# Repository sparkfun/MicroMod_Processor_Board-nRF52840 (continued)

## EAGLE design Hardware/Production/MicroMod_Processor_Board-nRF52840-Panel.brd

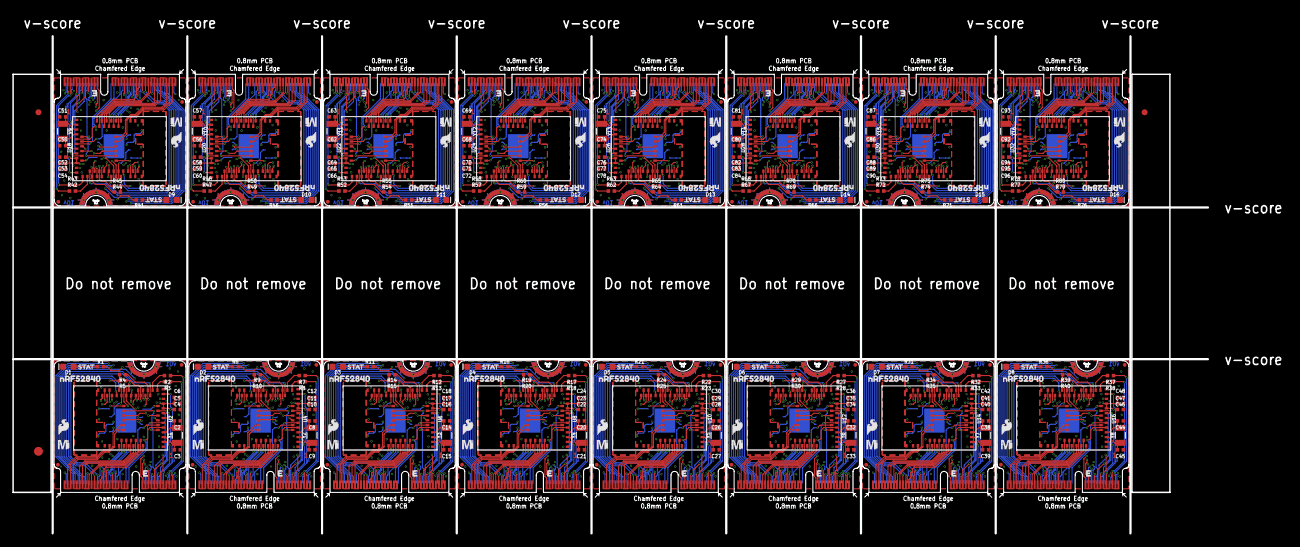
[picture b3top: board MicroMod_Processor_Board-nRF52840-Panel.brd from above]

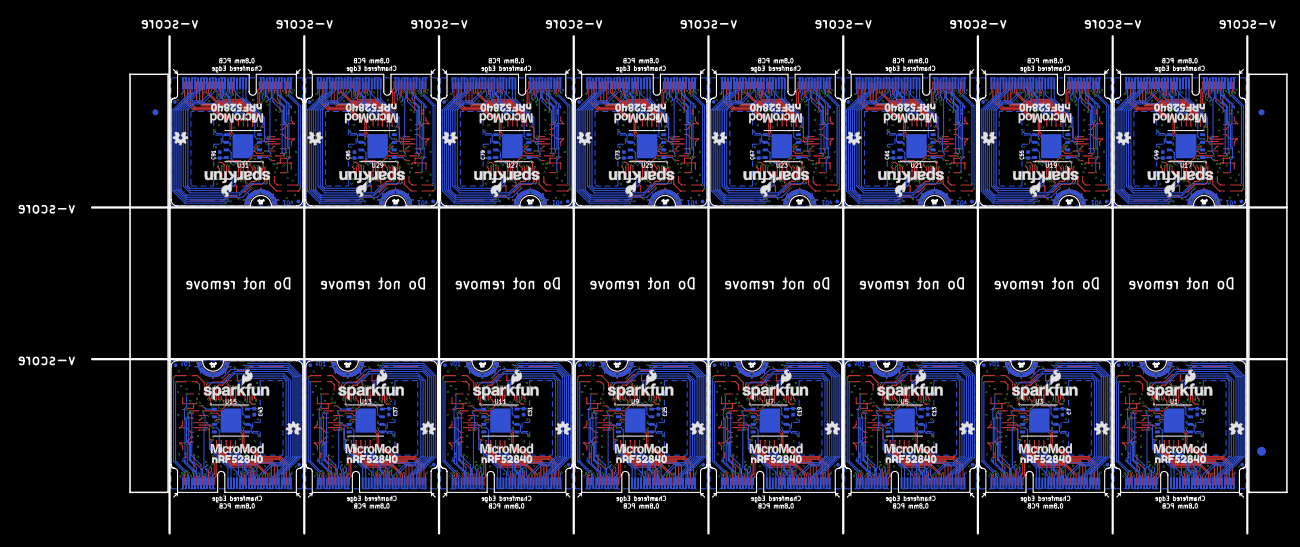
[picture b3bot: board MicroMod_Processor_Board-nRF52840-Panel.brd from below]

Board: 4 copper layers, 199.6 x 83.1 mm, 454 parts (131 on the bottom side), 928 nets.

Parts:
C1, C6, C7, C12, C13, C18, C19, C24, C25, C30, C31, C36, C37, C42, C43, C48, C49, C54, C55, C60, C61, C66, C67, C72, C73, C78, C79, C84, C85, C90, C91, C96: 0.1uF; 0402-TIGHT
C2, C3, C8, C9, C14, C15, C20, C21, C26, C27, C32, C33, C38, C39, C44, C45, C50, C51, C56, C57, C62, C63, C68, C69, C74, C75, C80, C81, C86, C87, C92, C93: 15pF; 0402-TIGHT
C4, C5, C10, C11, C16, C17, C22, C23, C28, C29, C34, C35, C40, C41, C46, C47, C52, C53, C58, C59, C64, C65, C70, C71, C76, C77, C82, C83, C88, C89, C94, C95: 10uF; 0402-TIGHT
D1, D2, D3, D4, D5, D6, D7, D8, D9, D10, D11, D12, D13, D14, D15, D16: BLUE; LED-0603
E$1, E$2, E$3, E$4: FIDUCIAL-1X2
E$5, E$6: FIDUCIAL-1.5X3
FD1, FD2, FD3, FD4, FD5, FD6, FD7, FD8, FD9, FD10, FD11, FD12, FD13, FD14, FD15, FD16, FD17, FD18, FD19, FD20, FD21, FD22, FD23, FD24, FD25, FD26, FD27, FD28, FD29, FD30, FD31, FD32, FD33, FD34, FD35, FD36, FD37, FD38, FD39, FD40, FD41, FD42, FD43, FD44, FD45, FD46, FD47, FD48, FD49, FD50, FD51, FD52, FD53, FD54, FD55, FD56, FD57, FD58, FD59, FD60, FD61, FD62, FD63, FD64: FIDUCIALUFIDUCIAL; FIDUCIAL-MICRO
J1, J2, J3, J4, J5, J6, J7, J8, J9, J10, J11, J12, J13, J14, J15, J16: MICROMOD-2222; M.2-CARD-E-22
LOGO1, LOGO5, LOGO8, LOGO11, LOGO14, LOGO17, LOGO20, LOGO23, LOGO26, LOGO29, LOGO32, LOGO35, LOGO38, LOGO41, LOGO44, LOGO47: SFE_LOGO_NAME_FLAME.1_INCH; SFE_LOGO_NAME_FLAME_.1
LOGO2, LOGO6, LOGO9, LOGO12, LOGO15, LOGO18, LOGO21, LOGO24, LOGO27, LOGO30, LOGO33, LOGO36, LOGO39, LOGO42, LOGO45, LOGO48: SFE_LOGO_FLAME.1_INCH; SFE_LOGO_FLAME_.1
LOGO3, LOGO4, LOGO7, LOGO10, LOGO13, LOGO16, LOGO19, LOGO22, LOGO25, LOGO28, LOGO31, LOGO34, LOGO37, LOGO40, LOGO43, LOGO46: OSHW-LOGOMINI; OSHW-LOGO-MINI
R1, R6, R11, R16, R21, R26, R31, R36, R41, R46, R51, R56, R61, R66, R71, R76: 1k; 0402-TIGHT
R2, R3, R7, R8, R12, R13, R17, R18, R22, R23, R27, R28, R32, R33, R37, R38, R42, R43, R47, R48, R52, R53, R57, R58, R62, R63, R67, R68, R72, R73, R77, R78: 27OHM; 0402-TIGHT
R4, R5, R9, R10, R14, R15, R19, R20, R24, R25, R29, R30, R34, R35, R39, R40, R44, R45, R49, R50, R54, R55, R59, R60, R64, R65, R69, R70, R74, R75, R79, R80: 10k; 0402-TIGHT
U1, U3, U5, U7, U9, U11, U13, U15, U17, U19, U21, U23, U25, U27, U29, U31: W25QXX128MBIT-6X5; WSON-8-6X5
U2, U4, U6, U8, U10, U12, U14, U16, U18, U20, U22, U24, U26, U28, U30, U32: MDBT50Q
U$1, U$7, U$12, U$17, U$22, U$27, U$32, U$37, U$42, U$47, U$52, U$57, U$62, U$67, U$72, U$77: MICROMOD_MI_LOGO_.35
U$2, U$3, U$9, U$10, U$14, U$15, U$19, U$20, U$24, U$25, U$29, U$30, U$34, U$35, U$39, U$40, U$44, U$45, U$49, U$50, U$54, U$55, U$59, U$60, U$64, U$65, U$69, U$70, U$74, U$75, U$79, U$80: NRF528400
U$4, U$6, U$11, U$16, U$21, U$26, U$31, U$36, U$41, U$46, U$51, U$56, U$61, U$66, U$71, U$76: STAT_TO_32
U$5, U$8, U$13, U$18, U$23, U$28, U$33, U$38, U$43, U$48, U$53, U$58, U$63, U$68, U$73, U$78: MICROMOD_LOGO_.35
Y1, Y2, Y3, Y4, Y5, Y6, Y7, Y8, Y9, Y10, Y11, Y12, Y13, Y14, Y15, Y16: 32.768kHz; CRYSTAL-SMD-3.2X1.5MM

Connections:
3.3V: C1.1, C4.1, C5.1, C6.1, J1.2, J1.74, R4.2, R5.2, U1.8, U2.28, U2.30
3.3V1: C7.1, C10.1, C11.1, C12.1, J2.2, J2.74, R9.2, R10.2, U3.8, U4.28, U4.30
3.3V2: C13.1, C16.1, C17.1, C18.1, J3.2, J3.74, R14.2, R15.2, U5.8, U6.28, U6.30
3.3V3: C19.1, C22.1, C23.1, C24.1, J4.2, J4.74, R19.2, R20.2, U7.8, U8.28, U8.30
3.3V4: C25.1, C28.1, C29.1, C30.1, J5.2, J5.74, R24.2, R25.2, U9.8, U10.28, U10.30
3.3V5: C31.1, C34.1, C35.1, C36.1, J6.2, J6.74, R29.2, R30.2, U11.8, U12.28, U12.30
3.3V6: C37.1, C40.1, C41.1, C42.1, J7.2, J7.74, R34.2, R35.2, U13.8, U14.28, U14.30
3.3V7: C43.1, C46.1, C47.1, C48.1, J8.2, J8.74, R39.2, R40.2, U15.8, U16.28, U16.30
3.3V8: C49.1, C52.1, C53.1, C54.1, J9.2, J9.74, R44.2, R45.2, U17.8, U18.28, U18.30
3.3V9: C55.1, C58.1, C59.1, C60.1, J10.2, J10.74, R49.2, R50.2, U19.8, U20.28, U20.30
3.3V10: C61.1, C64.1, C65.1, C66.1, J11.2, J11.74, R54.2, R55.2, U21.8, U22.28, U22.30
3.3V11: C67.1, C70.1, C71.1, C72.1, J12.2, J12.74, R59.2, R60.2, U23.8, U24.28, U24.30
3.3V12: C73.1, C76.1, C77.1, C78.1, J13.2, J13.74, R64.2, R65.2, U25.8, U26.28, U26.30
3.3V13: C79.1, C82.1, C83.1, C84.1, J14.2, J14.74, R69.2, R70.2, U27.8, U28.28, U28.30
3.3V14: C85.1, C88.1, C89.1, C90.1, J15.2, J15.74, R74.2, R75.2, U29.8, U30.28, U30.30
3.3V15: C91.1, C94.1, C95.1, C96.1, J16.2, J16.74, R79.2, R80.2, U31.8, U32.28, U32.30
!BOOT!: J1.11, R4.1, U2.37
!BOOT!1: J2.11, R9.1, U4.37
!BOOT!2: J3.11, R14.1, U6.37
!BOOT!3: J4.11, R19.1, U8.37
!BOOT!4: J5.11, R24.1, U10.37
!BOOT!5: J6.11, R29.1, U12.37
!BOOT!6: J7.11, R34.1, U14.37
!BOOT!7: J8.11, R39.1, U16.37
!BOOT!8: J9.11, R44.1, U18.37
!BOOT!9: J10.11, R49.1, U20.37
!BOOT!10: J11.11, R54.1, U22.37
!BOOT!11: J12.11, R59.1, U24.37
!BOOT!12: J13.11, R64.1, U26.37
!BOOT!13: J14.11, R69.1, U28.37
!BOOT!14: J15.11, R74.1, U30.37
!BOOT!15: J16.11, R79.1, U32.37
!RESET!: J1.6, R5.1, U2.40
!RESET!1: J2.6, R10.1, U4.40
!RESET!2: J3.6, R15.1, U6.40
!RESET!3: J4.6, R20.1, U8.40
!RESET!4: J5.6, R25.1, U10.40
!RESET!5: J6.6, R30.1, U12.40
!RESET!6: J7.6, R35.1, U14.40
!RESET!7: J8.6, R40.1, U16.40
!RESET!8: J9.6, R45.1, U18.40
!RESET!9: J10.6, R50.1, U20.40
!RESET!10: J11.6, R55.1, U22.40
!RESET!11: J12.6, R60.1, U24.40
!RESET!12: J13.6, R65.1, U26.40
!RESET!13: J14.6, R70.1, U28.40
!RESET!14: J15.6, R75.1, U30.40
!RESET!15: J16.6, R80.1, U32.40
ADC0: J1.34, U2.20
ADC1: J1.38, U2.21
ADC2: J2.34, U4.20
ADC3: J2.38, U4.21
ADC4: J3.34, U6.20
ADC5: J3.38, U6.21
ADC6: J4.34, U8.20
ADC7: J4.38, U8.21
ADC8: J5.34, U10.20
ADC9: J5.38, U10.21
ADC10: J6.34, U12.20
ADC11: J6.38, U12.21
ADC12: J7.34, U14.20
ADC13: J7.38, U14.21
ADC14: J8.34, U16.20
ADC15: J8.38, U16.21
ADC16: J9.34, U18.20
ADC17: J9.38, U18.21
ADC18: J10.34, U20.20
ADC19: J10.38, U20.21
ADC20: J11.34, U22.20
ADC21: J11.38, U22.21
ADC22: J12.34, U24.20
ADC23: J12.38, U24.21
ADC24: J13.34, U26.20
ADC25: J13.38, U26.21
ADC26: J14.34, U28.20
ADC27: J14.38, U28.21
ADC28: J15.34, U30.20
ADC29: J15.38, U30.21
ADC30: J16.34, U32.20
ADC31: J16.38, U32.21
ADC_D+: J1.63, U2.10
ADC_D+1: J2.63, U4.10
ADC_D+2: J3.63, U6.10
ADC_D+3: J4.63, U8.10
ADC_D+4: J5.63, U10.10
ADC_D+5: J6.63, U12.10
ADC_D+6: J7.63, U14.10
ADC_D+7: J8.63, U16.10
ADC_D+8: J9.63, U18.10
ADC_D+9: J10.63, U20.10
ADC_D+10: J11.63, U22.10
ADC_D+11: J12.63, U24.10
ADC_D+12: J13.63, U26.10
ADC_D+13: J14.63, U28.10
ADC_D+14: J15.63, U30.10
ADC_D+15: J16.63, U32.10
ADC_D-: J1.65, U2.9
ADC_D-1: J2.65, U4.9
ADC_D-2: J3.65, U6.9
ADC_D-3: J4.65, U8.9
ADC_D-4: J5.65, U10.9
ADC_D-5: J6.65, U12.9
ADC_D-6: J7.65, U14.9
ADC_D-7: J8.65, U16.9
ADC_D-8: J9.65, U18.9
ADC_D-9: J10.65, U20.9
ADC_D-10: J11.65, U22.9
ADC_D-11: J12.65, U24.9
ADC_D-12: J13.65, U26.9
ADC_D-13: J14.65, U28.9
ADC_D-14: J15.65, U30.9
ADC_D-15: J16.65, U32.9
BATT_VIN/1: J2.49, U4.14
BATT_VIN/2: J3.49, U6.14
BATT_VIN/3: J1.49, U2.14
BATT_VIN/4: J4.49, U8.14
BATT_VIN/5: J5.49, U10.14
BATT_VIN/6: J6.49, U12.14
BATT_VIN/7: J7.49, U14.14
BATT_VIN/8: J8.49, U16.14
BATT_VIN/9: J9.49, U18.14
BATT_VIN/10: J10.49, U20.14
BATT_VIN/11: J11.49, U22.14
BATT_VIN/12: J12.49, U24.14
BATT_VIN/13: J13.49, U26.14
BATT_VIN/14: J14.49, U28.14
BATT_VIN/15: J15.49, U30.14
BATT_VIN/16: J16.49, U32.14
CTS1: J1.15, U2.26
CTS2: J2.15, U4.26
CTS3: J3.15, U6.26
CTS4: J4.15, U8.26
CTS5: J5.15, U10.26
CTS6: J6.15, U12.26
CTS7: J7.15, U14.26
CTS8: J8.15, U16.26
CTS9: J9.15, U18.26
CTS10: J10.15, U20.26
CTS11: J11.15, U22.26
CTS12: J12.15, U24.26
CTS13: J13.15, U26.26
CTS14: J14.15, U28.26
CTS15: J15.15, U30.26
CTS16: J16.15, U32.26
D0: J1.10, U2.16
D1: J1.18, U2.25
D2: J2.10, U4.16
D3: J2.18, U4.25
D4: J3.10, U6.16
D5: J3.18, U6.25
D6: J4.10, U8.16
D7: J4.18, U8.25
D8: J5.10, U10.16
D9: J5.18, U10.25
D10: J6.10, U12.16
D11: J6.18, U12.25
D12: J7.10, U14.16
D13: J7.18, U14.25
D14: J8.10, U16.16
D15: J8.18, U16.25
D16: J9.10, U18.16
D17: J9.18, U18.25
D18: J10.10, U20.16
D19: J10.18, U20.25
D20: J11.10, U22.16
D21: J11.18, U22.25
D22: J12.10, U24.16
D23: J12.18, U24.25
D24: J13.10, U26.16
D25: J13.18, U26.25
D26: J14.10, U28.16
D27: J14.18, U28.25
D28: J15.10, U30.16
D29: J15.18, U30.25
D30: J16.10, U32.16
D31: J16.18, U32.25
FLASH_!CS!: U1.1, U2.29
FLASH_!CS!1: U3.1, U4.29
FLASH_!CS!2: U5.1, U6.29
FLASH_!CS!3: U7.1, U8.29
FLASH_!CS!4: U9.1, U10.29
FLASH_!CS!5: U11.1, U12.29
FLASH_!CS!6: U13.1, U14.29
FLASH_!CS!7: U15.1, U16.29
FLASH_!CS!8: U17.1, U18.29
FLASH_!CS!9: U19.1, U20.29
FLASH_!CS!10: U21.1, U22.29
FLASH_!CS!11: U23.1, U24.29
FLASH_!CS!12: U25.1, U26.29
FLASH_!CS!13: U27.1, U28.29
FLASH_!CS!14: U29.1, U30.29
FLASH_!CS!15: U31.1, U32.29
GND: C1.2, C2.1, C3.1, C4.2, C5.2, C6.2, D1.C, J1.1, J1.7, J1.33, J1.36, J1.39, J1.45, J1.75, J1.GND1, J1.GND2, J1.GND3, U1.4, U2.1, U2.2, U2.15, U2.33, U2.55
GND1: C7.2, C8.1, C9.1, C10.2, C11.2, C12.2, D2.C, J2.1, J2.7, J2.33, J2.36, J2.39, J2.45, J2.75, J2.GND1, J2.GND2, J2.GND3, U3.4, U4.1, U4.2, U4.15, U4.33, U4.55
GND2: C13.2, C14.1, C15.1, C16.2, C17.2, C18.2, D3.C, J3.1, J3.7, J3.33, J3.36, J3.39, J3.45, J3.75, J3.GND1, J3.GND2, J3.GND3, U5.4, U6.1, U6.2, U6.15, U6.33, U6.55
GND3: C19.2, C20.1, C21.1, C22.2, C23.2, C24.2, D4.C, J4.1, J4.7, J4.33, J4.36, J4.39, J4.45, J4.75, J4.GND1, J4.GND2, J4.GND3, U7.4, U8.1, U8.2, U8.15, U8.33, U8.55
GND4: C25.2, C26.1, C27.1, C28.2, C29.2, C30.2, D5.C, J5.1, J5.7, J5.33, J5.36, J5.39, J5.45, J5.75, J5.GND1, J5.GND2, J5.GND3, U9.4, U10.1, U10.2, U10.15, U10.33, U10.55
GND5: C31.2, C32.1, C33.1, C34.2, C35.2, C36.2, D6.C, J6.1, J6.7, J6.33, J6.36, J6.39, J6.45, J6.75, J6.GND1, J6.GND2, J6.GND3, U11.4, U12.1, U12.2, U12.15, U12.33, U12.55
GND6: C37.2, C38.1, C39.1, C40.2, C41.2, C42.2, D7.C, J7.1, J7.7, J7.33, J7.36, J7.39, J7.45, J7.75, J7.GND1, J7.GND2, J7.GND3, U13.4, U14.1, U14.2, U14.15, U14.33, U14.55
GND7: C43.2, C44.1, C45.1, C46.2, C47.2, C48.2, D8.C, J8.1, J8.7, J8.33, J8.36, J8.39, J8.45, J8.75, J8.GND1, J8.GND2, J8.GND3, U15.4, U16.1, U16.2, U16.15, U16.33, U16.55
GND8: C49.2, C50.1, C51.1, C52.2, C53.2, C54.2, D9.C, J9.1, J9.7, J9.33, J9.36, J9.39, J9.45, J9.75, J9.GND1, J9.GND2, J9.GND3, U17.4, U18.1, U18.2, U18.15, U18.33, U18.55
GND9: C55.2, C56.1, C57.1, C58.2, C59.2, C60.2, D10.C, J10.1, J10.7, J10.33, J10.36, J10.39, J10.45, J10.75, J10.GND1, J10.GND2, J10.GND3, U19.4, U20.1, U20.2, U20.15, U20.33, U20.55
GND10: C61.2, C62.1, C63.1, C64.2, C65.2, C66.2, D11.C, J11.1, J11.7, J11.33, J11.36, J11.39, J11.45, J11.75, J11.GND1, J11.GND2, J11.GND3, U21.4, U22.1, U22.2, U22.15, U22.33, U22.55
GND11: C67.2, C68.1, C69.1, C70.2, C71.2, C72.2, D12.C, J12.1, J12.7, J12.33, J12.36, J12.39, J12.45, J12.75, J12.GND1, J12.GND2, J12.GND3, U23.4, U24.1, U24.2, U24.15, U24.33, U24.55
GND12: C73.2, C74.1, C75.1, C76.2, C77.2, C78.2, D13.C, J13.1, J13.7, J13.33, J13.36, J13.39, J13.45, J13.75, J13.GND1, J13.GND2, J13.GND3, U25.4, U26.1, U26.2, U26.15, U26.33, U26.55
GND13: C79.2, C80.1, C81.1, C82.2, C83.2, C84.2, D14.C, J14.1, J14.7, J14.33, J14.36, J14.39, J14.45, J14.75, J14.GND1, J14.GND2, J14.GND3, U27.4, U28.1, U28.2, U28.15, U28.33, U28.55
GND14: C85.2, C86.1, C87.1, C88.2, C89.2, C90.2, D15.C, J15.1, J15.7, J15.33, J15.36, J15.39, J15.45, J15.75, J15.GND1, J15.GND2, J15.GND3, U29.4, U30.1, U30.2, U30.15, U30.33, U30.55
GND15: C91.2, C92.1, C93.1, C94.2, C95.2, C96.2, D16.C, J16.1, J16.7, J16.33, J16.36, J16.39, J16.45, J16.75, J16.GND1, J16.GND2, J16.GND3, U31.4, U32.1, U32.2, U32.15, U32.33, U32.55
GPIO0: J1.40, U2.8
GPIO1: J1.42, U2.7
GPIO2: J1.44, U2.6
GPIO3: J1.46, U2.5
GPIO4: J1.48, U2.4
GPIO5: J1.73, U2.3
GPIO6: J1.71, U2.57
GPIO7: J1.69, U2.56
GPIO8: J2.73, U4.3
GPIO9: J2.69, U4.56
GPIO10: J2.71, U4.57
GPIO11: J2.42, U4.7
GPIO12: J2.46, U4.5
GPIO13: J2.44, U4.6
GPIO14: J2.48, U4.4
GPIO15: J2.40, U4.8
GPIO16: J3.73, U6.3
GPIO17: J3.69, U6.56
GPIO18: J3.71, U6.57
GPIO19: J3.42, U6.7
GPIO20: J3.46, U6.5
GPIO21: J3.44, U6.6
GPIO22: J3.48, U6.4
GPIO23: J3.40, U6.8
GPIO24: J4.73, U8.3
GPIO25: J4.69, U8.56
GPIO26: J4.71, U8.57
GPIO27: J4.42, U8.7
GPIO28: J4.46, U8.5
GPIO29: J4.44, U8.6
GPIO30: J4.48, U8.4
GPIO31: J4.40, U8.8
GPIO32: J5.73, U10.3
GPIO33: J5.69, U10.56
GPIO34: J5.71, U10.57
GPIO35: J5.42, U10.7
GPIO36: J5.46, U10.5
GPIO37: J5.44, U10.6
GPIO38: J5.48, U10.4
GPIO39: J5.40, U10.8
GPIO40: J6.73, U12.3
GPIO41: J6.69, U12.56
GPIO42: J6.71, U12.57
GPIO43: J6.42, U12.7
GPIO44: J6.46, U12.5
GPIO45: J6.44, U12.6
GPIO46: J6.48, U12.4
GPIO47: J6.40, U12.8
GPIO48: J7.73, U14.3
GPIO49: J7.69, U14.56
GPIO50: J7.71, U14.57
GPIO51: J7.42, U14.7
GPIO52: J7.46, U14.5
GPIO53: J7.44, U14.6
GPIO54: J7.48, U14.4
GPIO55: J7.40, U14.8
GPIO56: J8.73, U16.3
GPIO57: J8.69, U16.56
GPIO58: J8.71, U16.57
GPIO59: J8.42, U16.7
GPIO60: J8.46, U16.5
GPIO61: J8.44, U16.6
GPIO62: J8.48, U16.4
GPIO63: J8.40, U16.8
GPIO64: J9.73, U18.3
GPIO65: J9.69, U18.56
GPIO66: J9.71, U18.57
GPIO67: J9.42, U18.7
GPIO68: J9.46, U18.5
GPIO69: J9.44, U18.6
GPIO70: J9.48, U18.4
GPIO71: J9.40, U18.8
GPIO72: J10.73, U20.3
GPIO73: J10.69, U20.56
GPIO74: J10.71, U20.57
GPIO75: J10.42, U20.7
GPIO76: J10.46, U20.5
GPIO77: J10.44, U20.6
GPIO78: J10.48, U20.4
GPIO79: J10.40, U20.8
GPIO80: J11.73, U22.3
GPIO81: J11.69, U22.56
GPIO82: J11.71, U22.57
GPIO83: J11.42, U22.7
GPIO84: J11.46, U22.5
GPIO85: J11.44, U22.6
GPIO86: J11.48, U22.4
GPIO87: J11.40, U22.8
GPIO88: J12.73, U24.3
GPIO89: J12.69, U24.56
GPIO90: J12.71, U24.57
GPIO91: J12.42, U24.7
GPIO92: J12.46, U24.5
GPIO93: J12.44, U24.6
GPIO94: J12.48, U24.4
GPIO95: J12.40, U24.8
GPIO96: J13.73, U26.3
GPIO97: J13.69, U26.56
GPIO98: J13.71, U26.57
GPIO99: J13.42, U26.7
GPIO100: J13.46, U26.5
GPIO101: J13.44, U26.6
GPIO102: J13.48, U26.4
GPIO103: J13.40, U26.8
GPIO104: J14.73, U28.3
GPIO105: J14.69, U28.56
GPIO106: J14.71, U28.57
GPIO107: J14.42, U28.7
GPIO108: J14.46, U28.5
GPIO109: J14.44, U28.6
GPIO110: J14.48, U28.4
GPIO111: J14.40, U28.8
GPIO112: J15.73, U30.3
GPIO113: J15.69, U30.56
GPIO114: J15.71, U30.57
GPIO115: J15.42, U30.7
GPIO116: J15.46, U30.5
GPIO117: J15.44, U30.6
GPIO118: J15.48, U30.4
GPIO119: J15.40, U30.8
GPIO120: J16.73, U32.3
GPIO121: J16.69, U32.56
GPIO122: J16.71, U32.57
GPIO123: J16.42, U32.7
GPIO124: J16.46, U32.5
GPIO125: J16.44, U32.6
GPIO126: J16.48, U32.4
GPIO127: J16.40, U32.8
I2C_!INT!: J1.16, U2.60
I2C_!INT!1: J2.16, U4.60
I2C_!INT!2: J3.16, U6.60
I2C_!INT!3: J4.16, U8.60
I2C_!INT!4: J5.16, U10.60
I2C_!INT!5: J6.16, U12.60
I2C_!INT!6: J7.16, U14.60
I2C_!INT!7: J8.16, U16.60
I2C_!INT!8: J9.16, U18.60
I2C_!INT!9: J10.16, U20.60
I2C_!INT!10: J11.16, U22.60
I2C_!INT!11: J12.16, U24.60
I2C_!INT!12: J13.16, U26.60
I2C_!INT!13: J14.16, U28.60
I2C_!INT!14: J15.16, U30.60
I2C_!INT!15: J16.16, U32.60
LED_BUILTIN: R1.2, U2.23
LED_BUILTIN1: R6.2, U4.23
LED_BUILTIN2: R11.2, U6.23
LED_BUILTIN3: R16.2, U8.23
LED_BUILTIN4: R21.2, U10.23
LED_BUILTIN5: R26.2, U12.23
LED_BUILTIN6: R31.2, U14.23
LED_BUILTIN7: R36.2, U16.23
LED_BUILTIN8: R41.2, U18.23
LED_BUILTIN9: R46.2, U20.23
LED_BUILTIN10: R51.2, U22.23
LED_BUILTIN11: R56.2, U24.23
LED_BUILTIN12: R61.2, U26.23
LED_BUILTIN13: R66.2, U28.23
LED_BUILTIN14: R71.2, U30.23
LED_BUILTIN15: R76.2, U32.23
unnamed: R2.2, U2.35
unnamed: D1.A, R1.1
unnamed: R3.2, U2.34
unnamed: C3.2, U2.17, Y1.P$1
unnamed: D2.A, R6.1
unnamed: C2.2, U2.18, Y1.P$2
unnamed: R7.2, U4.35
unnamed: R8.2, U4.34
unnamed: C9.2, U4.17, Y2.P$1
unnamed: C8.2, U4.18, Y2.P$2
unnamed: D3.A, R11.1
unnamed: R12.2, U6.35
unnamed: R13.2, U6.34
unnamed: C15.2, U6.17, Y3.P$1
unnamed: C14.2, U6.18, Y3.P$2
unnamed: D4.A, R16.1
unnamed: R17.2, U8.35
unnamed: R18.2, U8.34
unnamed: C21.2, U8.17, Y4.P$1
unnamed: C20.2, U8.18, Y4.P$2
unnamed: D5.A, R21.1
unnamed: R22.2, U10.35
unnamed: R23.2, U10.34
unnamed: C27.2, U10.17, Y5.P$1
unnamed: C26.2, U10.18, Y5.P$2
unnamed: D6.A, R26.1
unnamed: R27.2, U12.35
unnamed: R28.2, U12.34
unnamed: C33.2, U12.17, Y6.P$1
unnamed: C32.2, U12.18, Y6.P$2
unnamed: D7.A, R31.1
unnamed: R32.2, U14.35
unnamed: R33.2, U14.34
unnamed: C39.2, U14.17, Y7.P$1
unnamed: C38.2, U14.18, Y7.P$2
unnamed: D8.A, R36.1
unnamed: R37.2, U16.35
unnamed: R38.2, U16.34
unnamed: C45.2, U16.17, Y8.P$1
unnamed: C44.2, U16.18, Y8.P$2
unnamed: D9.A, R41.1
unnamed: R42.2, U18.35
unnamed: R43.2, U18.34
unnamed: C51.2, U18.17, Y9.P$1
unnamed: C50.2, U18.18, Y9.P$2
unnamed: D10.A, R46.1
unnamed: R47.2, U20.35
unnamed: R48.2, U20.34
unnamed: C57.2, U20.17, Y10.P$1
unnamed: C56.2, U20.18, Y10.P$2
unnamed: D11.A, R51.1
unnamed: R52.2, U22.35
unnamed: R53.2, U22.34
unnamed: C63.2, U22.17, Y11.P$1
unnamed: C62.2, U22.18, Y11.P$2
unnamed: D12.A, R56.1
unnamed: R57.2, U24.35
unnamed: R58.2, U24.34
unnamed: C69.2, U24.17, Y12.P$1
unnamed: C68.2, U24.18, Y12.P$2
unnamed: D13.A, R61.1
unnamed: R62.2, U26.35
unnamed: R63.2, U26.34
unnamed: C75.2, U26.17, Y13.P$1
unnamed: C74.2, U26.18, Y13.P$2
unnamed: D14.A, R66.1
unnamed: R67.2, U28.35
unnamed: R68.2, U28.34
unnamed: C81.2, U28.17, Y14.P$1
unnamed: C80.2, U28.18, Y14.P$2
unnamed: D15.A, R71.1
unnamed: R72.2, U30.35
unnamed: R73.2, U30.34
unnamed: C87.2, U30.17, Y15.P$1
unnamed: C86.2, U30.18, Y15.P$2
unnamed: D16.A, R76.1
unnamed: R77.2, U32.35
unnamed: R78.2, U32.34
unnamed: C93.2, U32.17, Y16.P$1
unnamed: C92.2, U32.18, Y16.P$2
NFC1: J1.43, U2.52
NFC2: J1.41, U2.54
NFC3: J2.43, U4.52
NFC4: J2.41, U4.54
NFC5: J3.43, U6.52
NFC6: J3.41, U6.54
NFC7: J4.43, U8.52
NFC8: J4.41, U8.54
NFC9: J5.43, U10.52
NFC10: J5.41, U10.54
NFC11: J6.43, U12.52
NFC12: J6.41, U12.54
NFC13: J7.43, U14.52
NFC14: J7.41, U14.54
NFC15: J8.43, U16.52
NFC16: J8.41, U16.54
NFC17: J9.43, U18.52
NFC18: J9.41, U18.54
NFC19: J10.43, U20.52
NFC20: J10.41, U20.54
NFC21: J11.43, U22.52
NFC22: J11.41, U22.54
NFC23: J12.43, U24.52
NFC24: J12.41, U24.54
NFC25: J13.43, U26.52
NFC26: J13.41, U26.54
NFC27: J14.43, U28.52
NFC28: J14.41, U28.54
NFC29: J15.43, U30.52
NFC30: J15.41, U30.54
NFC31: J16.43, U32.52
NFC32: J16.41, U32.54
PDM_CLK: J1.50, U2.49
PDM_CLK1: J2.50, U4.49
PDM_CLK2: J3.50, U6.49
PDM_CLK3: J4.50, U8.49
PDM_CLK4: J5.50, U10.49
PDM_CLK5: J6.50, U12.49
PDM_CLK6: J7.50, U14.49
PDM_CLK7: J8.50, U16.49
PDM_CLK8: J9.50, U18.49
PDM_CLK9: J10.50, U20.49
PDM_CLK10: J11.50, U22.49
PDM_CLK11: J12.50, U24.49
PDM_CLK12: J13.50, U26.49
PDM_CLK13: J14.50, U28.49
PDM_CLK14: J15.50, U30.49
PDM_CLK15: J16.50, U32.49
PDM_DATA: J1.52, U2.19
PDM_DATA1: J2.52, U4.19
PDM_DATA2: J3.52, U6.19
PDM_DATA3: J4.52, U8.19
PDM_DATA4: J5.52, U10.19
PDM_DATA5: J6.52, U12.19
PDM_DATA6: J7.52, U14.19
PDM_DATA7: J8.52, U16.19
PDM_DATA8: J9.52, U18.19
PDM_DATA9: J10.52, U20.19
PDM_DATA10: J11.52, U22.19
PDM_DATA11: J12.52, U24.19
PDM_DATA12: J13.52, U26.19
PDM_DATA13: J14.52, U28.19
PDM_DATA14: J15.52, U30.19
PDM_DATA15: J16.52, U32.19
PWM0: J1.32, U2.22
PWM1: J1.47, U2.38
PWM2: J2.32, U4.22
PWM3: J2.47, U4.38
PWM4: J3.32, U6.22
PWM5: J3.47, U6.38
PWM6: J4.32, U8.22
PWM7: J4.47, U8.38
PWM8: J5.32, U10.22
PWM9: J5.47, U10.38
PWM10: J6.32, U12.22
PWM11: J6.47, U12.38
PWM12: J7.32, U14.22
PWM13: J7.47, U14.38
PWM14: J8.32, U16.22
PWM15: J8.47, U16.38
PWM16: J9.32, U18.22
PWM17: J9.47, U18.38
PWM18: J10.32, U20.22
PWM19: J10.47, U20.38
PWM20: J11.32, U22.22
PWM21: J11.47, U22.38
PWM22: J12.32, U24.22
PWM23: J12.47, U24.38
PWM24: J13.32, U26.22
PWM25: J13.47, U26.38
PWM26: J14.32, U28.22
PWM27: J14.47, U28.38
PWM28: J15.32, U30.22
PWM29: J15.47, U30.38
PWM30: J16.32, U32.22
PWM31: J16.47, U32.38
RTS1: J1.13, U2.50
RTS2: J2.13, U4.50
RTS3: J3.13, U6.50
RTS4: J4.13, U8.50
RTS5: J5.13, U10.50
RTS6: J6.13, U12.50
RTS7: J7.13, U14.50
RTS8: J8.13, U16.50
RTS9: J9.13, U18.50
RTS10: J10.13, U20.50
RTS11: J11.13, U22.50
RTS12: J12.13, U24.50
RTS13: J13.13, U26.50
RTS14: J14.13, U28.50
RTS15: J15.13, U30.50
RTS16: J16.13, U32.50
RX1: J1.19, U2.41
RX2: J1.20, U2.59
RX3: J2.19, U4.41
RX4: J2.20, U4.59
RX5: J3.19, U6.41
RX6: J3.20, U6.59
RX7: J4.19, U8.41
RX8: J4.20, U8.59
RX9: J5.19, U10.41
RX10: J5.20, U10.59
RX11: J6.19, U12.41
RX12: J6.20, U12.59
RX13: J7.19, U14.41
RX14: J7.20, U14.59
RX15: J8.19, U16.41
RX16: J8.20, U16.59
RX17: J9.19, U18.41
RX18: J9.20, U18.59
RX19: J10.19, U20.41
RX20: J10.20, U20.59
RX21: J11.19, U22.41
RX22: J11.20, U22.59
RX23: J12.19, U24.41
RX24: J12.20, U24.59
RX25: J13.19, U26.41
RX26: J13.20, U26.59
RX27: J14.19, U28.41
RX28: J14.20, U28.59
RX29: J15.19, U30.41
RX30: J15.20, U30.59
RX31: J16.19, U32.41
RX32: J16.20, U32.59
SCL: J1.14, U2.27
SCL1: J1.53, U2.48
SCL2: J2.14, U4.27
SCL3: J2.53, U4.48
SCL4: J3.14, U6.27
SCL5: J3.53, U6.48
SCL6: J4.14, U8.27
SCL7: J4.53, U8.48
SCL8: J5.14, U10.27
SCL9: J5.53, U10.48
SCL10: J6.14, U12.27
SCL11: J6.53, U12.48
SCL12: J7.14, U14.27
SCL13: J7.53, U14.48
SCL14: J8.14, U16.27
SCL15: J8.53, U16.48
SCL16: J9.14, U18.27
SCL17: J9.53, U18.48
SCL18: J10.14, U20.27
SCL19: J10.53, U20.48
SCL20: J11.14, U22.27
SCL21: J11.53, U22.48
SCL22: J12.14, U24.27
SCL23: J12.53, U24.48
SCL24: J13.14, U26.27
SCL25: J13.53, U26.48
SCL26: J14.14, U28.27
SCL27: J14.53, U28.48
SCL28: J15.14, U30.27
SCL29: J15.53, U30.48
SCL30: J16.14, U32.27
SCL31: J16.53, U32.48
SDA: J1.12, U2.24
SDA1: J1.51, U2.61
SDA2: J2.12, U4.24
SDA3: J2.51, U4.61
SDA4: J3.12, U6.24
SDA5: J3.51, U6.61
SDA6: J4.12, U8.24
SDA7: J4.51, U8.61
SDA8: J5.12, U10.24
SDA9: J5.51, U10.61
SDA10: J6.12, U12.24
SDA11: J6.51, U12.61
SDA12: J7.12, U14.24
SDA13: J7.51, U14.61
SDA14: J8.12, U16.24
SDA15: J8.51, U16.61
SDA16: J9.12, U18.24
SDA17: J9.51, U18.61
SDA18: J10.12, U20.24
SDA19: J10.51, U20.61
SDA20: J11.12, U22.24
SDA21: J11.51, U22.61
SDA22: J12.12, U24.24
SDA23: J12.51, U24.61
SDA24: J13.12, U26.24
SDA25: J13.51, U26.61
SDA26: J14.12, U28.24
SDA27: J14.51, U28.61
SDA28: J15.12, U30.24
SDA29: J15.51, U30.61
SDA30: J16.12, U32.24
SDA31: J16.51, U32.61
SDIO_DATA1: J1.66, U1.2, U2.46
SDIO_DATA2: J1.68, U1.3, U2.45
SDIO_DATA3: J2.66, U3.2, U4.46
SDIO_DATA4: J2.68, U3.3, U4.45
SDIO_DATA5: J3.66, U5.2, U6.46
SDIO_DATA6: J3.68, U5.3, U6.45
SDIO_DATA7: J4.66, U7.2, U8.46
SDIO_DATA8: J4.68, U7.3, U8.45
SDIO_DATA9: J5.66, U9.2, U10.46
SDIO_DATA10: J5.68, U9.3, U10.45
SDIO_DATA11: J6.66, U11.2, U12.46
SDIO_DATA12: J6.68, U11.3, U12.45
SDIO_DATA13: J7.66, U13.2, U14.46
SDIO_DATA14: J7.68, U13.3, U14.45
SDIO_DATA15: J8.66, U15.2, U16.46
SDIO_DATA16: J8.68, U15.3, U16.45
SDIO_DATA17: J9.66, U17.2, U18.46
SDIO_DATA18: J9.68, U17.3, U18.45
SDIO_DATA19: J10.66, U19.2, U20.46
SDIO_DATA20: J10.68, U19.3, U20.45
SDIO_DATA21: J11.66, U21.2, U22.46
SDIO_DATA22: J11.68, U21.3, U22.45
SDIO_DATA23: J12.66, U23.2, U24.46
SDIO_DATA24: J12.68, U23.3, U24.45
SDIO_DATA25: J13.66, U25.2, U26.46
SDIO_DATA26: J13.68, U25.3, U26.45
SDIO_DATA27: J14.66, U27.2, U28.46
SDIO_DATA28: J14.68, U27.3, U28.45
SDIO_DATA29: J15.66, U29.2, U30.46
SDIO_DATA30: J15.68, U29.3, U30.45
SDIO_DATA31: J16.66, U31.2, U32.46
SDIO_DATA32: J16.68, U31.3, U32.45
SPI_!CS!: J1.70, U1.7, U2.47
SPI_!CS!1: J1.55, U2.44
SPI_!CS!2: J2.70, U3.7, U4.47
SPI_!CS!3: J2.55, U4.44
SPI_!CS!4: J3.70, U5.7, U6.47
SPI_!CS!5: J3.55, U6.44
SPI_!CS!6: J4.70, U7.7, U8.47
SPI_!CS!7: J4.55, U8.44
SPI_!CS!8: J5.70, U9.7, U10.47
SPI_!CS!9: J5.55, U10.44
SPI_!CS!10: J6.70, U11.7, U12.47
SPI_!CS!11: J6.55, U12.44
SPI_!CS!12: J7.70, U13.7, U14.47
SPI_!CS!13: J7.55, U14.44
SPI_!CS!14: J8.70, U15.7, U16.47
SPI_!CS!15: J8.55, U16.44
SPI_!CS!16: J9.70, U17.7, U18.47
SPI_!CS!17: J9.55, U18.44
SPI_!CS!18: J10.70, U19.7, U20.47
SPI_!CS!19: J10.55, U20.44
SPI_!CS!20: J11.70, U21.7, U22.47
SPI_!CS!21: J11.55, U22.44
SPI_!CS!22: J12.70, U23.7, U24.47
SPI_!CS!23: J12.55, U24.44
SPI_!CS!24: J13.70, U25.7, U26.47
SPI_!CS!25: J13.55, U26.44
SPI_!CS!26: J14.70, U27.7, U28.47
SPI_!CS!27: J14.55, U28.44
SPI_!CS!28: J15.70, U29.7, U30.47
SPI_!CS!29: J15.55, U30.44
SPI_!CS!30: J16.70, U31.7, U32.47
SPI_!CS!31: J16.55, U32.44
SPI_MISO: J1.64, U1.5, U2.43
SPI_MISO1: J1.61, U2.11
SPI_MISO2: J2.64, U3.5, U4.43
SPI_MISO3: J2.61, U4.11
SPI_MISO4: J3.64, U5.5, U6.43
SPI_MISO5: J3.61, U6.11
SPI_MISO6: J4.64, U7.5, U8.43
SPI_MISO7: J4.61, U8.11
SPI_MISO8: J5.64, U9.5, U10.43
SPI_MISO9: J5.61, U10.11
SPI_MISO10: J6.64, U11.5, U12.43
SPI_MISO11: J6.61, U12.11
SPI_MISO12: J7.64, U13.5, U14.43
SPI_MISO13: J7.61, U14.11
SPI_MISO14: J8.64, U15.5, U16.43
SPI_MISO15: J8.61, U16.11
SPI_MISO16: J9.64, U17.5, U18.43
SPI_MISO17: J9.61, U18.11
SPI_MISO18: J10.64, U19.5, U20.43
SPI_MISO19: J10.61, U20.11
SPI_MISO20: J11.64, U21.5, U22.43
SPI_MISO21: J11.61, U22.11
SPI_MISO22: J12.64, U23.5, U24.43
SPI_MISO23: J12.61, U24.11
SPI_MISO24: J13.64, U25.5, U26.43
SPI_MISO25: J13.61, U26.11
SPI_MISO26: J14.64, U27.5, U28.43
SPI_MISO27: J14.61, U28.11
SPI_MISO28: J15.64, U29.5, U30.43
SPI_MISO29: J15.61, U30.11
SPI_MISO30: J16.64, U31.5, U32.43
SPI_MISO31: J16.61, U32.11
SPI_MOSI: J1.62, U2.36
SPI_MOSI1: J1.59, U2.12
SPI_MOSI2: J2.59, U4.12
SPI_MOSI3: J2.62, U4.36
SPI_MOSI4: J3.59, U6.12
SPI_MOSI5: J3.62, U6.36
SPI_MOSI6: J4.59, U8.12
SPI_MOSI7: J4.62, U8.36
SPI_MOSI8: J5.59, U10.12
SPI_MOSI9: J5.62, U10.36
SPI_MOSI10: J6.59, U12.12
SPI_MOSI11: J6.62, U12.36
SPI_MOSI12: J7.59, U14.12
SPI_MOSI13: J7.62, U14.36
SPI_MOSI14: J8.59, U16.12
SPI_MOSI15: J8.62, U16.36
SPI_MOSI16: J9.59, U18.12
SPI_MOSI17: J9.62, U18.36
SPI_MOSI18: J10.59, U20.12
SPI_MOSI19: J10.62, U20.36
SPI_MOSI20: J11.59, U22.12
SPI_MOSI21: J11.62, U22.36
SPI_MOSI22: J12.59, U24.12
SPI_MOSI23: J12.62, U24.36
SPI_MOSI24: J13.59, U26.12
SPI_MOSI25: J13.62, U26.36
SPI_MOSI26: J14.59, U28.12
SPI_MOSI27: J14.62, U28.36
SPI_MOSI28: J15.59, U30.12
SPI_MOSI29: J15.62, U30.36
SPI_MOSI30: J16.59, U32.12
SPI_MOSI31: J16.62, U32.36
SPI_SCK: J1.60, U1.6, U2.42
SPI_SCK1: J1.57, U2.13
SPI_SCK2: J2.57, U4.13
SPI_SCK3: J2.60, U3.6, U4.42
SPI_SCK4: J3.57, U6.13
SPI_SCK5: J3.60, U5.6, U6.42
SPI_SCK6: J4.57, U8.13
SPI_SCK7: J4.60, U7.6, U8.42
SPI_SCK8: J5.57, U10.13
SPI_SCK9: J5.60, U9.6, U10.42
SPI_SCK10: J6.57, U12.13
SPI_SCK11: J6.60, U11.6, U12.42
SPI_SCK12: J7.57, U14.13
SPI_SCK13: J7.60, U13.6, U14.42
SPI_SCK14: J8.57, U16.13
SPI_SCK15: J8.60, U15.6, U16.42
SPI_SCK16: J9.57, U18.13
SPI_SCK17: J9.60, U17.6, U18.42
SPI_SCK18: J10.57, U20.13
SPI_SCK19: J10.60, U19.6, U20.42
SPI_SCK20: J11.57, U22.13
SPI_SCK21: J11.60, U21.6, U22.42
SPI_SCK22: J12.57, U24.13
SPI_SCK23: J12.60, U23.6, U24.42
SPI_SCK24: J13.57, U26.13
SPI_SCK25: J13.60, U25.6, U26.42
SPI_SCK26: J14.57, U28.13
SPI_SCK27: J14.60, U27.6, U28.42
SPI_SCK28: J15.57, U30.13
SPI_SCK29: J15.60, U29.6, U30.42
SPI_SCK30: J16.57, U32.13
SPI_SCK31: J16.60, U31.6, U32.42
SWDCK: J1.21, U2.53
SWDCK1: J2.21, U4.53
SWDCK2: J3.21, U6.53
SWDCK3: J4.21, U8.53
SWDCK4: J5.21, U10.53
SWDCK5: J6.21, U12.53
SWDCK6: J7.21, U14.53
SWDCK7: J8.21, U16.53
SWDCK8: J9.21, U18.53
SWDCK9: J10.21, U20.53
SWDCK10: J11.21, U22.53
SWDCK11: J12.21, U24.53
SWDCK12: J13.21, U26.53
SWDCK13: J14.21, U28.53
SWDCK14: J15.21, U30.53
SWDCK15: J16.21, U32.53
SWDIO: J1.23, U2.51
SWDIO1: J2.23, U4.51
SWDIO2: J3.23, U6.51
SWDIO3: J4.23, U8.51
SWDIO4: J5.23, U10.51
SWDIO5: J6.23, U12.51
SWDIO6: J7.23, U14.51
SWDIO7: J8.23, U16.51
SWDIO8: J9.23, U18.51
SWDIO9: J10.23, U20.51
SWDIO10: J11.23, U22.51
SWDIO11: J12.23, U24.51
SWDIO12: J13.23, U26.51
SWDIO13: J14.23, U28.51
SWDIO14: J15.23, U30.51
SWDIO15: J16.23, U32.51
TX1: J1.17, U2.39
TX2: J1.22, U2.58
TX3: J2.17, U4.39
TX4: J2.22, U4.58
TX5: J3.17, U6.39
TX6: J3.22, U6.58
TX7: J4.17, U8.39
TX8: J4.22, U8.58
TX9: J5.17, U10.39
TX10: J5.22, U10.58
TX11: J6.17, U12.39
TX12: J6.22, U12.58
TX13: J7.17, U14.39
TX14: J7.22, U14.58
TX15: J8.17, U16.39
TX16: J8.22, U16.58
TX17: J9.17, U18.39
TX18: J9.22, U18.58
TX19: J10.17, U20.39
TX20: J10.22, U20.58
TX21: J11.17, U22.39
TX22: J11.22, U22.58
TX23: J12.17, U24.39
TX24: J12.22, U24.58
TX25: J13.17, U26.39
TX26: J13.22, U26.58
TX27: J14.17, U28.39
TX28: J14.22, U28.58
TX29: J15.17, U30.39
TX30: J15.22, U30.58
TX31: J16.17, U32.39
TX32: J16.22, U32.58
USB_D+: J1.3, R2.1
USB_D+1: J2.3, R7.1
USB_D+2: J3.3, R12.1
USB_D+3: J4.3, R17.1
USB_D+4: J5.3, R22.1
USB_D+5: J6.3, R27.1
USB_D+6: J7.3, R32.1
USB_D+7: J8.3, R37.1
USB_D+8: J9.3, R42.1
USB_D+9: J10.3, R47.1
USB_D+10: J11.3, R52.1
USB_D+11: J12.3, R57.1
USB_D+12: J13.3, R62.1
USB_D+13: J14.3, R67.1
USB_D+14: J15.3, R72.1
USB_D+15: J16.3, R77.1
USB_D-: J1.5, R3.1
USB_D-1: J2.5, R8.1
USB_D-2: J3.5, R13.1
USB_D-3: J4.5, R18.1
USB_D-4: J5.5, R23.1
USB_D-5: J6.5, R28.1
USB_D-6: J7.5, R33.1
USB_D-7: J8.5, R38.1
USB_D-8: J9.5, R43.1
USB_D-9: J10.5, R48.1
USB_D-10: J11.5, R53.1
USB_D-11: J12.5, R58.1
USB_D-12: J13.5, R63.1
USB_D-13: J14.5, R68.1
USB_D-14: J15.5, R73.1
USB_D-15: J16.5, R78.1
V_USB: J1.9, U2.32
V_USB1: J2.9, U4.32
V_USB2: J3.9, U6.32
V_USB3: J4.9, U8.32
V_USB4: J5.9, U10.32
V_USB5: J6.9, U12.32
V_USB6: J7.9, U14.32
V_USB7: J8.9, U16.32
V_USB8: J9.9, U18.32
V_USB9: J10.9, U20.32
V_USB10: J11.9, U22.32
V_USB11: J12.9, U24.32
V_USB12: J13.9, U26.32
V_USB13: J14.9, U28.32
V_USB14: J15.9, U30.32
V_USB15: J16.9, U32.32

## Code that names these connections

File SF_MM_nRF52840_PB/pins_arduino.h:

#pragma once
#include <stdint.h>
#include <macros.h>

#ifndef __PINS_ARDUINO__
#define __PINS_ARDUINO__

#define ANALOG_CONFIG

/* Analog reference options
 * Different possibilities available combining Reference and Gain
 */
enum _AnalogReferenceMode
{
  AR_VDD,         // 3.3 V
  AR_INTERNAL,    // 0.6 V
  AR_INTERNAL1V2, // 1.2 V
  AR_INTERNAL2V4  // 2.4 V
};

/* Analog acquisition time options */
enum _AnalogAcquisitionTime
{
  AT_3_US,
  AT_5_US,
  AT_10_US, // Default value
  AT_15_US,
  AT_20_US,
  AT_40_US
};

// Frequency of the board main oscillator
#define VARIANT_MAINOSC (32768ul)

// Master clock frequency
#define VARIANT_MCK (64000000ul)

// Pins
// ----
// Number of pins defined in PinDescription array
#ifdef __cplusplus
extern "C" unsigned int PINCOUNT_fn();
#endif
#define PINS_COUNT (PINCOUNT_fn())
#define NUM_DIGITAL_PINS (48u)
#define NUM_ANALOG_INPUTS (6u)
#define NUM_ANALOG_OUTPUTS (0u)

extern PinName digitalPinToPinName(pin_size_t P);       // add paulvha

// LEDs
// ----
#define PIN_LED (13u)
#define LED_BUILTIN PIN_LED

// Analog pins
// -----------
#define PIN_A0 (4u)
#define PIN_A1 (5u)
#define PIN_A2 (29u)
#define PIN_A3 (28u)
#define PIN_A4 (30u)
#define PIN_A5 (31u)
static const uint8_t A0 = PIN_A0;
static const uint8_t A1 = PIN_A1;
static const uint8_t A2 = PIN_A2;
static const uint8_t A3 = PIN_A3;
static const uint8_t A4 = PIN_A4;
static const uint8_t A5 = PIN_A5;
#define PIN_PWM0 (6u)
#define PIN_PWM1 (16u)
static const uint8_t PWM0 = PIN_PWM0;
static const uint8_t PWM1 = PIN_PWM1;
#define PIN_BATTVIN3 (30u)
static const uint8_t BATTVIN3 = PIN_BATTVIN3;
#define ADC_RESOLUTION 12

// Digital pins
// -----------
#define D0 27
#define D1 40
#define G0 29
#define G1 3
#define G2 45
#define G3 44
#define G4 43
#define G5 17
#define G6 38
#define G7 36
#define G8 46
#define G9 9
#define G10 10

/*
 * Serial interfaces
 */
// Serial (EDBG)
#define PIN_SERIAL_RX1 (42ul)
#define PIN_SERIAL_TX1 (35ul)
//For serial flow control, uncomment lines 189 and 190
#define PIN_SERIAL_RTS1 (34ul)
#define PIN_SERIAL_CTS1 (41ul)

#define PIN_SERIAL_RX2 (37ul)
#define PIN_SERIAL_TX2 (39ul)

// SPI
#define PIN_SPI_CIPO (2u)
#define PIN_SPI_COPI (31u)
#define PIN_SPI_SCK (28u)
#define PIN_SPI_SS (20u)

// //NOTE: this is for onboard flash IC
// #define PIN_SPI_CIPO (21u)
// #define PIN_SPI_COPI (14u)
// #define PIN_SPI_SCK (19u)
// #define PIN_SPI_SS (12u)

static const uint8_t SS = PIN_SPI_SS;
static const uint8_t MOSI = PIN_SPI_COPI;
static const uint8_t MISO = PIN_SPI_CIPO;
static const uint8_t SCK = PIN_SPI_SCK;

#define PIN_SPI_CIPO1 (21u)
#define PIN_SPI_COPI1 (14u)
#define PIN_SPI_SCK1 (19u)
#define PIN_SPI_SS1 (32u)

static const uint8_t SS1 = PIN_SPI_SS1;
static const uint8_t MOSI1 = PIN_SPI_COPI1;
static const uint8_t MISO1 = PIN_SPI_CIPO1;
static const uint8_t SCK1 = PIN_SPI_SCK1;

#define PIN_QSPI_SCK 19
#define PIN_QSPI_CS 14
#define PIN_QSPI_IO0 21
#define PIN_QSPI_IO1 22
#define PIN_QSPI_IO2 23
#define PIN_QSPI_IO3 32

// Wire
#define PIN_WIRE_SDA (8u)
#define PIN_WIRE_SCL (11u)
#define PIN_WIRE_INT (15u)

#define PIN_WIRE_SDA1 (33u)
#define PIN_WIRE_SCL1 (24u)

// PDM Interfaces
// ---------------
#define PIN_PDM_PWR (46)
#define PIN_PDM_CLK (25)
#define PIN_PDM_DIN (26)

// These serial port names are intended to allow libraries and architecture-neutral
// sketches to automatically default to the correct port name for a particular type
// of use.  For example, a GPS module would normally connect to SERIAL_PORT_HARDWARE_OPEN,
// the first hardware serial port whose RX/TX pins are not dedicated to another use.
//
// SERIAL_PORT_MONITOR        Port which normally prints to the Arduino Serial Monitor
//
// SERIAL_PORT_USBVIRTUAL     Port which is USB virtual serial
//
// SERIAL_PORT_LINUXBRIDGE    Port which connects to a Linux system via Bridge library
//
// SERIAL_PORT_HARDWARE       Hardware serial port, physical RX & TX pins.
//
// SERIAL_PORT_HARDWARE_OPEN  Hardware serial ports which are open for use.  Their RX & TX
//                            pins are NOT connected to anything by default.
#define SERIAL_PORT_USBVIRTUAL SerialUSB
#define SERIAL_PORT_MONITOR SerialUSB
#define SERIAL_PORT_HARDWARE Serial1
#define SERIAL_PORT_HARDWARE_OPEN Serial1

// Mbed specific defines
#define SERIAL_HOWMANY 2
#define SERIAL1_TX (digitalPinToPinName(PIN_SERIAL_TX1))
#define SERIAL1_RX (digitalPinToPinName(PIN_SERIAL_RX1))
//Uncomment the following two lines if you want to implement serial flow control
// #define SERIAL1_RTS (digitalPinToPinName(PIN_SERIAL_RTS1))
// #define SERIAL1_CTS (digitalPinToPinName(PIN_SERIAL_CTS1))
#define SERIAL2_TX (digitalPinToPinName(PIN_SERIAL_TX2))
#define SERIAL2_RX (digitalPinToPinName(PIN_SERIAL_RX2))

#define SERIAL_CDC 1
#define HAS_UNIQUE_ISERIAL_DESCRIPTOR
#define BOARD_VENDORID 0x2341
#define BOARD_PRODUCTID 0x805a
#define BOARD_NAME "Nano 33 BLE"

#define DFU_MAGIC_SERIAL_ONLY_RESET 0xb0

#define WIRE_HOWMANY 2

#define I2C_SDA (digitalPinToPinName(PIN_WIRE_SDA))
#define I2C_SCL (digitalPinToPinName(PIN_WIRE_SCL))
#define I2C_SDA1 (digitalPinToPinName(PIN_WIRE_SDA1))
#define I2C_SCL1 (digitalPinToPinName(PIN_WIRE_SCL1))

#define SPI_HOWMANY 2

#define SPI_MISO (digitalPinToPinName(PIN_SPI_CIPO))
#define SPI_MOSI (digitalPinToPinName(PIN_SPI_COPI))
#define SPI_SCK (digitalPinToPinName(PIN_SPI_SCK))

#define SPI_MISO1 (digitalPinToPinName(PIN_SPI_CIPO1))
#define SPI_MOSI1 (digitalPinToPinName(PIN_SPI_COPI1))
#define SPI_SCK1 (digitalPinToPinName(PIN_SPI_SCK1))

#define digitalPinToPort(P) (digitalPinToPinName(P) / 32)

uint8_t getUniqueSerialNumber(uint8_t *name);
void _ontouch1200bps_();

#endif //__PINS_ARDUINO__

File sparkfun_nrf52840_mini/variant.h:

/*
  Copyright (c) 2014-2015 Arduino LLC.  All right reserved.
  Copyright (c) 2016 Sandeep Mistry All right reserved.
  Copyright (c) 2018, Adafruit Industries (adafruit.com)

  This library is free software; you can redistribute it and/or
  modify it under the terms of the GNU Lesser General Public
  License as published by the Free Software Foundation; either
  version 2.1 of the License, or (at your option) any later version.
  This library is distributed in the hope that it will be useful,
  but WITHOUT ANY WARRANTY; without even the implied warranty of
  MERCHANTABILITY or FITNESS FOR A PARTICULAR PURPOSE.
  See the GNU Lesser General Public License for more details.
  You should have received a copy of the GNU Lesser General Public
  License along with this library; if not, write to the Free Software
  Foundation, Inc., 51 Franklin St, Fifth Floor, Boston, MA  02110-1301  USA
*/

#ifndef _VARIANT_SPARKFUN52840MINI_
#define _VARIANT_SPARKFUN52840MINI_

/** Master clock frequency */
#define VARIANT_MCK (64000000ul)

#define USE_LFXO // Board uses 32khz crystal for LF
// define USE_LFRC    // Board uses RC for LF

/*----------------------------------------------------------------------------
 *        Headers
 *----------------------------------------------------------------------------*/

#include "WVariant.h"

#ifdef __cplusplus
extern "C"
{
#endif // __cplusplus

// Number of pins defined in PinDescription array
#define PINS_COUNT (64)
#define NUM_DIGITAL_PINS (64)
#define NUM_ANALOG_INPUTS (8)
#define NUM_ANALOG_OUTPUTS (0)

// LEDs
#define PIN_LED1 (7)
#define LED_BUILTIN PIN_LED1
#define LED_BLUE PIN_LED1
#define LED_STATE_ON 1 // State when LED is lit

//Microphone
#define PIN_PDM_DIN 26
#define PIN_PDM_CLK 25
#define PIN_PDM_PWR -1 //not used
/*
 * Digital pins
 */
#define PIN_D0 (27)
#define PIN_D1 (40)
#define PIN_G0 (47)
#define PIN_G1 (46)
#define PIN_G2 (45)
#define PIN_G3 (44)
#define PIN_G4 (43)
#define PIN_G5 (42)
#define PIN_G6 (38)
#define PIN_G7 (36)
#define PIN_PWM0 (6)
#define PIN_PWM1 (16)

  static const uint8_t D0 = PIN_D0;
  static const uint8_t D1 = PIN_D1;
  static const uint8_t G0 = PIN_G0;
  static const uint8_t G1 = PIN_G1;
  static const uint8_t G2 = PIN_G2;
  static const uint8_t G3 = PIN_G3;
  static const uint8_t G4 = PIN_G4;
  static const uint8_t G5 = PIN_G5;
  static const uint8_t G6 = PIN_G6;
  static const uint8_t G7 = PIN_G7;
  static const uint8_t PWM0 = PIN_PWM0;
  static const uint8_t PWM1 = PIN_PWM1;

/*
 * Analog pins
 */
#define PIN_A0 (4)
#define PIN_A1 (5)
#define PIN_BATTVIN3 (30)

  static const uint8_t A0 = PIN_A0;
  static const uint8_t A1 = PIN_A1;
  static const uint8_t BATTVIN3 = PIN_BATTVIN3;
#define ADC_RESOLUTION 14 //TODO: not sure this is right

// Other pins
#define PIN_AREF (2)
#define PIN_DFU (13)
#define PIN_NFC1 (9)
#define PIN_NFC2 (10)

  static const uint8_t AREF = PIN_AREF;

  /*
 * Serial interfaces
 */

#define PIN_SERIAL1_RX (17)
#define PIN_SERIAL1_TX (15)
#define PIN_SERIAL1_CTS (41)
#define PIN_SERIAL1_RTS (34)

#define PIN_SERIAL2_RX (37)
#define PIN_SERIAL2_TX (39)

/*
 * SPI Interfaces
 */
#define SPI_INTERFACES_COUNT 2

#define PIN_SPI_MISO (21)
#define PIN_SPI_MOSI (14)
#define PIN_SPI_SCK (19)

  static const uint8_t SS = 32;
  static const uint8_t MOSI = PIN_SPI_MOSI;
  static const uint8_t MISO = PIN_SPI_MISO;
  static const uint8_t SCK = PIN_SPI_SCK;

//NOTE: this is actually the second SPI interface
#define PIN_SPI1_MISO (2)
#define PIN_SPI1_MOSI (31)
#define PIN_SPI1_SCK (28)

  static const uint8_t SS1 = 20;
  static const uint8_t MOSI1 = PIN_SPI1_MOSI;
  static const uint8_t MISO1 = PIN_SPI1_MISO;
  static const uint8_t SCK1 = PIN_SPI1_SCK;

// //NOTE: this is for external flash
// #define PIN_SPI_MISO (22)
// #define PIN_SPI_MOSI (21)
// #define PIN_SPI_SCK (19)

//   static const uint8_t SS = 12;
//   static const uint8_t MOSI = PIN_SPI_MOSI;
//   static const uint8_t MISO = PIN_SPI_MISO;
//   static const uint8_t SCK = PIN_SPI_SCK;

/*
 * Wire Interfaces
 */
#define WIRE_INTERFACES_COUNT 2

#define PIN_WIRE_SDA (8)
#define PIN_WIRE_SCL (11)

#define PIN_WIRE1_SDA (33)
#define PIN_WIRE1_SCL (24)

/*
 * QSPI interface for external flash
 */
#define PIN_QSPI_SCK 19
#define PIN_QSPI_CS 12
// #define PIN_QSPI_DATA0 34
// #define PIN_QSPI_DATA1 35
// #define PIN_QSPI_DATA2 36
// #define PIN_QSPI_DATA3 37
#define PIN_QSPI_IO0 21
#define PIN_QSPI_IO1 22
#define PIN_QSPI_IO2 23
#define PIN_QSPI_IO3 32

#define EXTERNAL_FLASH_USE_QSPI true

// On-board QSPI Flash
// If EXTERNAL_FLASH_DEVICES is not defined, all supported devices will be used
#define EXTERNAL_FLASH_DEVICES GD25Q16C

#ifdef __cplusplus
}
#endif

/*----------------------------------------------------------------------------
 *        Arduino objects - C++ only
 *----------------------------------------------------------------------------*/

#endif
